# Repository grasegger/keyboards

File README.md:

# Anna Keyboard

The Anna keyboard is a split ortholinear keyboard PCB with pads for kailh hotswap sockets. It has 5 columns and 4 rows on each side. It's built for usage with pro micro replacemets that have bluetooth, there is no ttrs jack.

## Firmware

You can find the zmk firmware for nice!nanos on [github.com/grasegger/zmk](https://github.com/grasegger/zmk). To build your own firmware use the zmk config repository setup and point to my zmk fork in your west.yml.

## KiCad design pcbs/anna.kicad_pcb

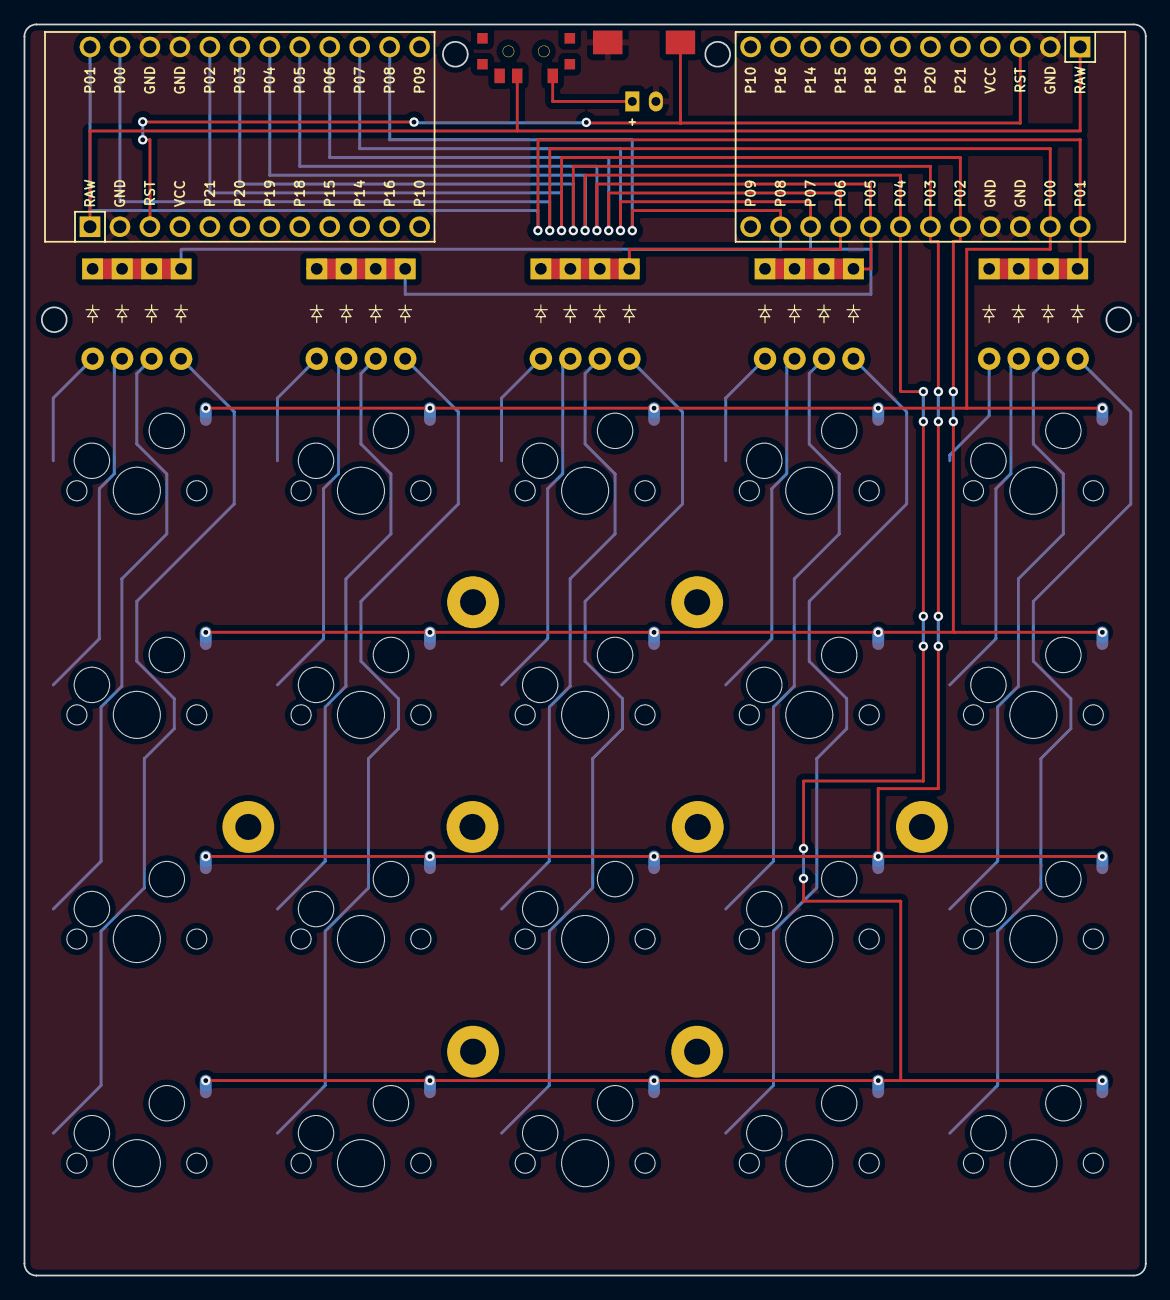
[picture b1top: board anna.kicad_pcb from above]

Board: 2 copper layers, 95.1 x 106.1 mm, 47 parts (0 on the bottom side), 43 nets.

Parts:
D1, D2, D3, D4, D5, D6, D7, D8, D9, D10, D11, D12, D13, D14, D15, D16, D17, D18, D19, D20: ComboDiode
JST1: JST_PH_S2B-PH-K_02x2.00mm_Angled
LED1, LED2: Tenting Puck
MCU1, MCU2: ProMicro
S1, S2, S3, S4, S5, S6, S7, S8, S9, S10, S11, S12, S13, S14, S15, S16, S17, S18, S19, S20: MX
T1: SPDT_C128955
_30: SW_SPST_REED_CT05-XXXX-J1

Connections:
BATPSWITCH: JST1.1, T1.1
DP1P0: D20.1, S20.1
DP1P2: D19.1, S19.1
DP1P3: D18.1, S18.1
DP1P4: D17.1, S17.1
DP5P0: D16.1, S16.1
DP5P2: D15.1, S15.1
DP5P3: D14.1, S14.1
DP5P4: D13.1, S13.1
DP6P0: D12.1, S12.1
DP6P2: D11.1, S11.1
DP6P3: D10.1, S10.1
DP6P4: D9.1, S9.1
DP7P0: D8.1, S8.1
DP7P2: D7.1, S7.1
DP7P3: D6.1, S6.1
DP7P4: D5.1, S5.1
DP8P0: D4.1, S4.1
DP8P2: D3.1, S3.1
DP8P3: D2.1, S2.1
DP8P4: D1.1, S1.1
GND: JST1.2, MCU1.2, MCU1.15, MCU1.16, MCU2.2, MCU2.15, MCU2.16, _30.1
P0: MCU1.14, MCU2.14, S4.2, S8.2, S12.2, S16.2, S20.2
P1: D17.2, D18.2, D19.2, D20.2, MCU1.13, MCU2.13
P2: MCU1.17, MCU2.17, S3.2, S7.2, S11.2, S15.2, S19.2
P3: MCU1.18, MCU2.18, S2.2, S6.2, S10.2, S14.2, S18.2
P4: MCU1.19, MCU2.19, S1.2, S5.2, S9.2, S13.2, S17.2
P5: D13.2, D14.2, D15.2, D16.2, MCU1.20, MCU2.20
P6: D9.2, D10.2, D11.2, D12.2, MCU1.21, MCU2.21
P7: D5.2, D6.2, D7.2, D8.2, MCU1.22, MCU2.22
P8: D1.2, D2.2, D3.2, D4.2, MCU1.23, MCU2.23
P9: MCU1.24, MCU2.24
P10: MCU1.12, MCU2.12
P14: MCU1.10, MCU2.10
P15: MCU1.9, MCU2.9
P16: MCU1.11, MCU2.11
P18: MCU1.8, MCU2.8
P19: MCU1.7, MCU2.7
P20: MCU1.6, MCU2.6
P21: MCU1.5, MCU2.5
RAW: MCU1.1, MCU2.1, T1.2
RST: MCU1.3, MCU2.3, _30.2
VCC: MCU1.4, MCU2.4

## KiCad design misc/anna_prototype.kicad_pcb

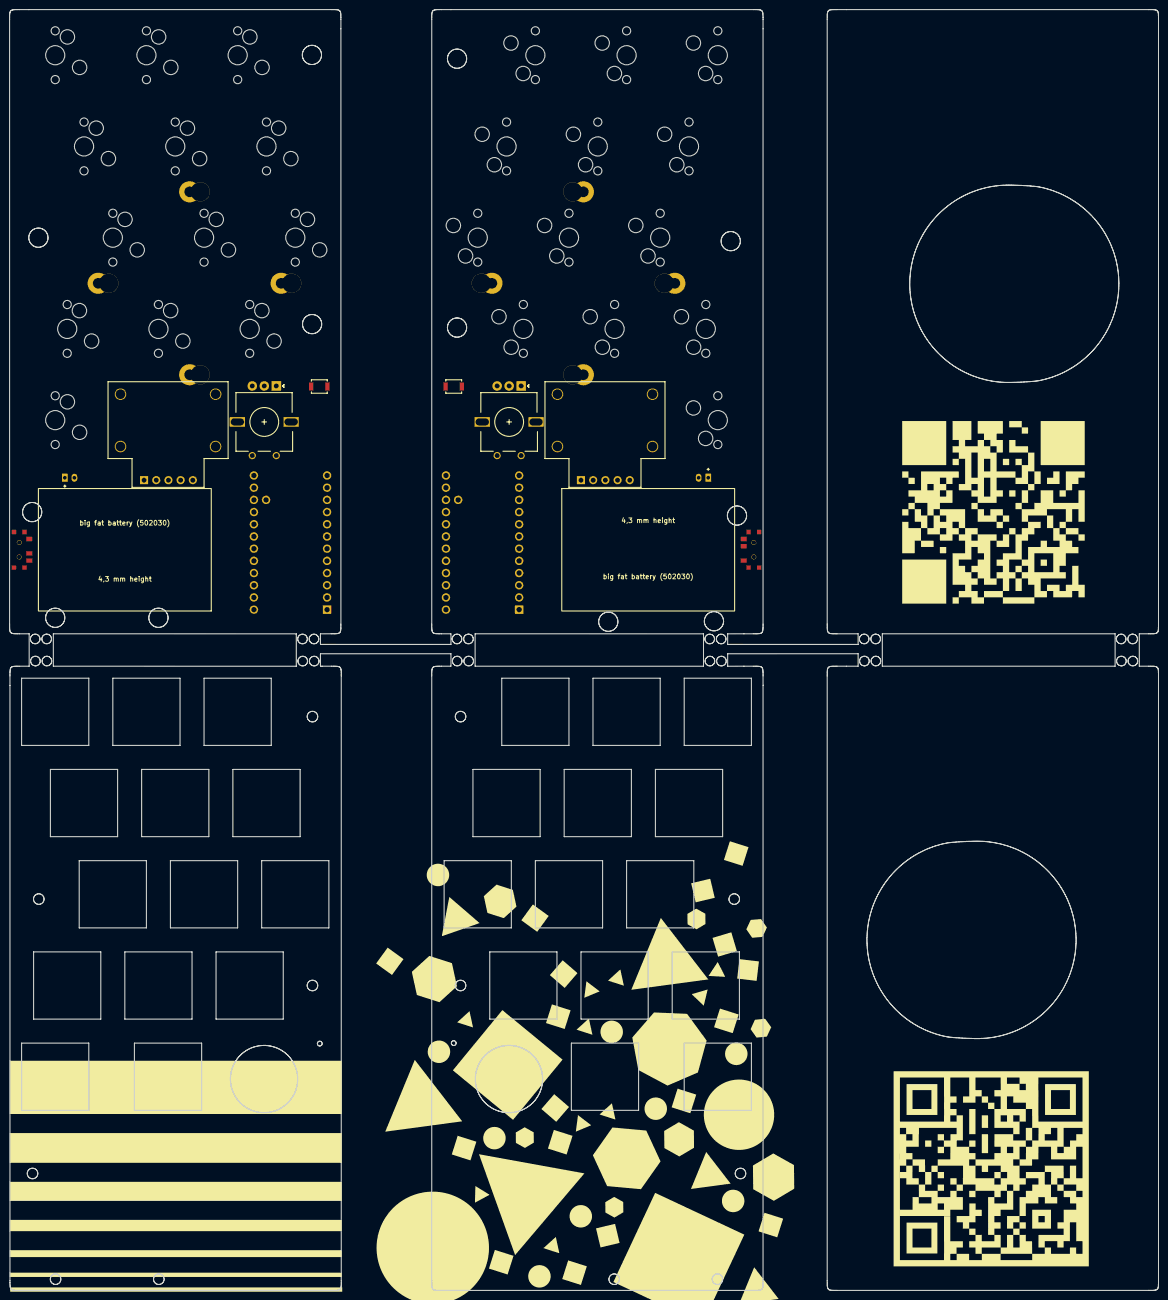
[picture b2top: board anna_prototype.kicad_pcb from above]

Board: 2 copper layers, 239.3 x 266.8 mm, 41 parts (0 on the bottom side), 24 nets, no tracks yet.

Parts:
JST1, JST2: JST_PH_S2B-PH-K_02x2.00mm_Angled
LED1, LED2: Tenting Puck
MCU1, MCU2: nice!nano
ROT1, ROT2: rotary_encoder
RSW2, RSW2#2: SW_Push; SW_SPST_B3U-1000P
S1, S2, S3, S4, S5, S6, S7, S8, S9, S10, S11, S12, S13, S14, S15, S16, S17, S18, S19, S20, S21, S22, S23, S24, S25, S26: MX
T1, T2: SPDT_C128955
_3, _6: pimoroni_trackball
svg2mod: G***; svg2mod

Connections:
BAT+: MCU1.1, MCU2.1, T1.2, T2.1
BATPSWITCH: JST1.1, JST2.1, T1.1, T2.2
GND: JST1.2, JST2.2, MCU1.2, MCU1.15, MCU1.16, MCU2.2, MCU2.15, MCU2.16, ROT1.2, ROT1.B, ROT2.2, ROT2.B, RSW2.2, RSW2#2.2, S1.2, S2.2, S3.2, S4.2, S5.2, S6.2, S7.2, S8.2, S9.2, S10.2, S11.2, S12.2, S13.2, S14.2, S15.2, S16.2, S17.2, S18.2, S19.2, S20.2, S21.2, S22.2, S23.2, S24.2, S25.2, S26.2
P002: MCU1.7, MCU2.7, S5.1, S18.1
P006: MCU1.13, MCU2.13
P008: MCU1.14, MCU2.14
P009: MCU1.12, MCU2.12, S3.1, S16.1
P010: MCU1.11, MCU2.11, S6.1, S19.1
P011: MCU1.22, MCU2.22, S4.1, S17.1
P017: MCU1.17, MCU2.17
P020: MCU1.18, MCU2.18, ROT1.1
P022: MCU1.19, MCU2.19, S13.1, S26.1
P024: MCU1.20, MCU2.20, S10.1, S23.1
P029: MCU1.6, MCU2.6, ROT1.C
P031: MCU1.5, MCU2.5, ROT1.A
P100: MCU1.21, MCU2.21
P101: MCU1.25, MCU2.25, S8.1, S21.1
P104: MCU1.23, MCU2.23, S1.1, S14.1
P106: MCU1.24, MCU2.24, ROT2.1, ROT2.A, ROT2.C, S7.1, S11.1, S20.1, S24.1
P111: MCU1.10, MCU2.10, S9.1, S22.1
P113: MCU1.9, MCU2.9, S12.1, S25.1
P115: MCU1.8, MCU2.8, S2.1, S15.1
RST: MCU1.3, MCU2.3, RSW2.1, RSW2#2.1
VCC: MCU1.4, MCU2.4

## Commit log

2021-10-11 Added ergogen submodule
2021-10-11 Some more basic stuff
2021-10-11 Update Makefile
2021-10-16 Submodule update
2021-10-23 ergogen updates
2021-10-23 update - just update
2021-10-23 Update Dockerfile
2021-11-20 Anna EDC
2021-11-20 Repo cleanup
2021-11-20 Dependency update
2021-11-20 Added warning
2021-11-20 Added preview render of the edc board
2021-11-23 Started work on the lasagna and made build process more robust
2021-11-23 Create LICENSE
2021-11-26 Added lasagna and its build process
2021-11-26 Tweaked routing for lasagna and added a preview.
2021-11-27 Updated lasagna with dhall and small improvements to the build process
2021-11-27 simplified some dhall
2021-11-27 Update ergogen
2021-11-28 Small fixes and updated info
2021-11-28 Install dhall to create ergogen config
2021-11-28 Removed pull request build from github actions
2021-11-28 Update ergogen dependency
2021-11-28 baby steps with actions
2021-11-28 Add proper cache
2021-11-28 Update cache config
2021-11-28 Trying to fix stuff
2021-11-28 Fixed submodule checkout
2021-11-28 Installing more packages
2021-11-28 Trying sudo for package install
2021-11-28 Installing less stuff now
2021-11-28 Install dependencies for running gui applications in a fake x buffer
2021-11-28 Made whole script reusable
2021-11-28 Fixed missing env prefix
2021-11-28 Exporting DSN within github actions
2021-11-28 Added xvfbwrapper to pip packages
2021-11-28 Added xdotool to package setup
2021-11-28 Added parameter to dsn export script
2021-11-28 Fixed some paths
2021-11-28 Trying to make process more robust
2021-11-28 Correct java version and no termination on error
2021-11-28 First freerouting in the cloud
2021-11-28 Uploading kicad and ses file to artifacts
2021-11-28 Fixed indent
2021-11-28 Gerber in Actions
2021-11-28 Fixed missing pipe
2021-11-28 Archive final pcb and gerbers
2021-11-28 Addes a missing job condition
2021-11-28 Export Previews
2021-11-28 Remove old build files
2021-11-28 Build PCBs in the cloud
2021-11-28 Better local building
2021-11-28 Flipped the mcu to the bottom on the lasagna
2021-11-28 more comfortable local make
2021-11-29 Smaller lasagna
2021-11-29 asdf
2021-11-29 Moved file
2021-11-29 Better build (#3)
2021-11-30 Pimoroni trackball updates for the lasagna
2021-11-30 Added screw holes to lasagna
2021-11-30 #2 Added shields for the lasagna
2021-11-30 Added bridge between pcbs again because of the autorouter
2021-12-01 Cleanup
2021-12-06 Remove shield
2021-12-06 Added weirdo board
2021-12-06 Fix CI
2022-01-24 Release of the anna
2022-01-25 Weirdo (#4)
